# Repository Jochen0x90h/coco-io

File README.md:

# CoCo IO

Input/Output (GPIO) module for CoCo

## Import
Add coco-io/\<version> to your conanfile where version corresponds to a git tag.

## Features
* Interface to GPIO pins
* Input interface for push buttons, rotary knobs, d-pads etc.

## Supported Platforms
See README.md of coco base library

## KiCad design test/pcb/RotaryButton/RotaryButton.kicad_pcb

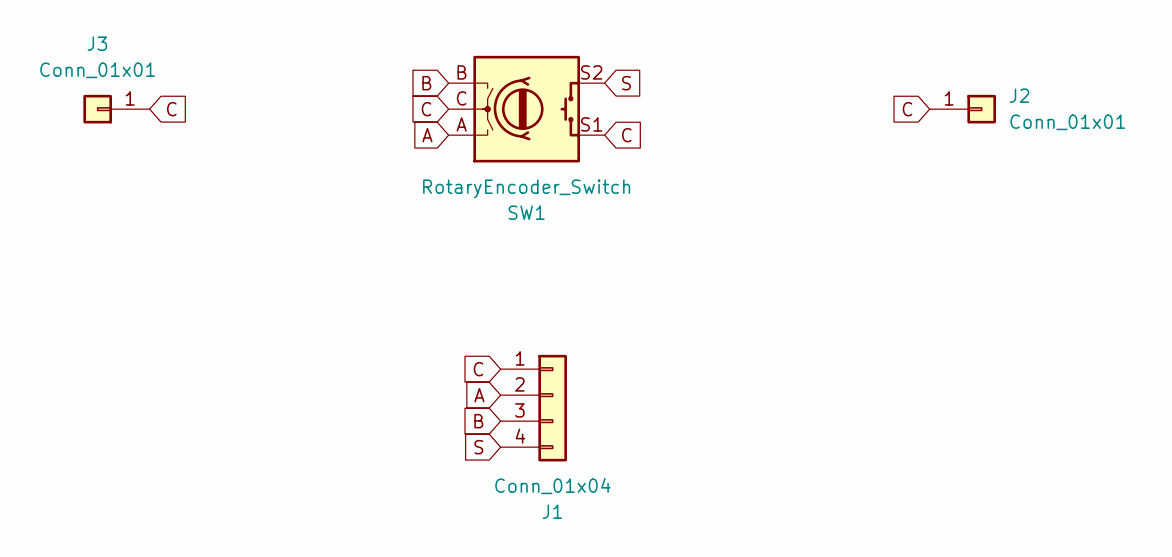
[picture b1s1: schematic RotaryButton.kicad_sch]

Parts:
J1: Conn_01x04; PinHeader_1x04_P2.54mm_Vertical
J2, J3: Conn_01x01; PinHeader_1x01_P2.54mm_Vertical
SW1: RotaryEncoder_Switch; PEC12R-4217F-S0024

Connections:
A: J1.2, SW1.A
B: J1.3, SW1.B
C: J1.1, J2.1, J3.1, SW1.C, SW1.S1
S: J1.4, SW1.S2

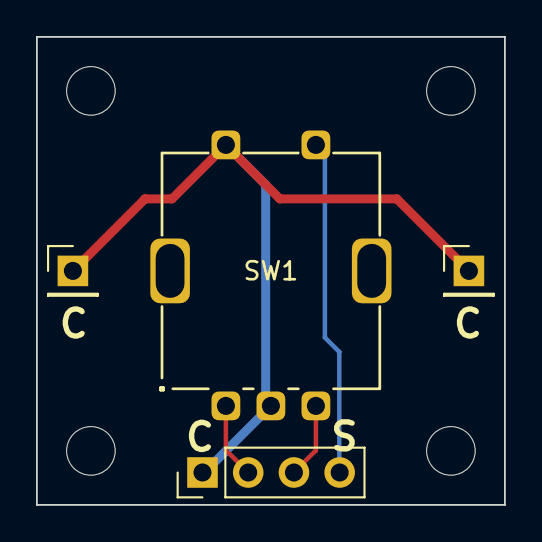
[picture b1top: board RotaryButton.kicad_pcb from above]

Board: 2 copper layers, 26.0 x 26.0 mm, 4 parts (0 on the bottom side), 4 nets.

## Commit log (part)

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2023-01-01 Version 0.1.0
2023-01-13 Add trigger
2023-01-13 Add trigger (#1)
2023-01-29 Loop is now a class
2023-01-29 Loop is now a class (#2)
2023-03-26 Use coco-toolchain
2023-04-30 Remove blocking calls
2023-05-17 Simplify configs
2023-05-18 Use coco-toolchain (#3)
    * Use coco-toolchain
    * Remove blocking calls
    * Simplify configs
2023-08-20 New input paradigm
2023-08-20 New input paradigm (#4)
2024-10-03 Use coco-device/0.3.0
2024-10-03 Use coco-device/0.3.0 (#5)
2026-01-29 Version 0.7.0
2026-02-22 Use new InputDevice
2026-02-22 Fix for linux
2026-03-01 Update test/pcb
2026-04-03 Remove need for coco-toolchain
2026-05-22 Use new handlers
2026-06-23 Use new CoroutineTaskList
